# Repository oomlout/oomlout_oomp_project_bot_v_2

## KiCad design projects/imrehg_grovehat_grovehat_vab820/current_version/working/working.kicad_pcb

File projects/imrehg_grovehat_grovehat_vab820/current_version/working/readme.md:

# grovehat
 
## summary 
* id: imrehg_grovehat_grovehat_vab820
* user: imrehg
* name: grovehat
* board: grovehat_vab820
* repo: https://github.com/imrehg/grovehat
* src_file_repo_kicad_pcb: grovehat-vab820.kicad_pcb
* src_file_repo_kicad_pcb_link: https://github.com/imrehg/grovehat/tree/master/grovehat-vab820.kicad_pcb

* src_file_repo_sch: grovehat-vab820.sch
* src_file_repo_sch_link: https://github.com/imrehg/grovehat/tree/master/grovehat-vab820.sch
* full details link: https://github.com/oomlout/oomlout_oomp_project_bot_v_2/tree/main/projects/imrehg_grovehat_grovehat_vab820/current_version/working

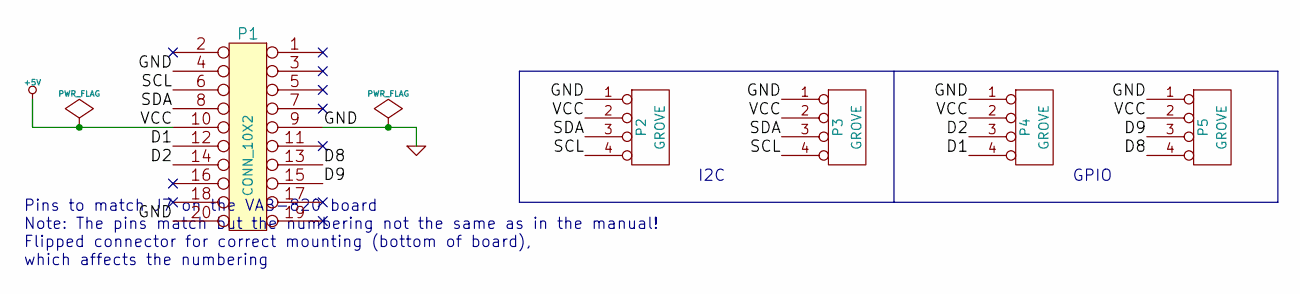
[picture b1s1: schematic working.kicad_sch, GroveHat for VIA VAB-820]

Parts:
P1: CONN_10X2; pin_array_2mm_10x2
P2, P3, P4, P5: GROVE; TWIG_2.0

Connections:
+5V: P1.10, P2.2, P3.2, P4.2, P5.2
/D1: P1.12, P4.4
/D2: P1.14, P4.3
/D8: P1.13, P5.4
/D9: P1.15, P5.3
/SCL: P1.6, P2.4, P3.4
/SDA: P1.8, P2.3, P3.3
GND: P1.4, P1.9, P1.20, P2.1, P3.1, P4.1, P5.1

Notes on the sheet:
Pins to match J7 on the VAB-820 board Note: The pins match but the numbering not the same as in the manual! Flipped connector for correct mounting (bottom of board), which affects the numbering
I2C
GPIO

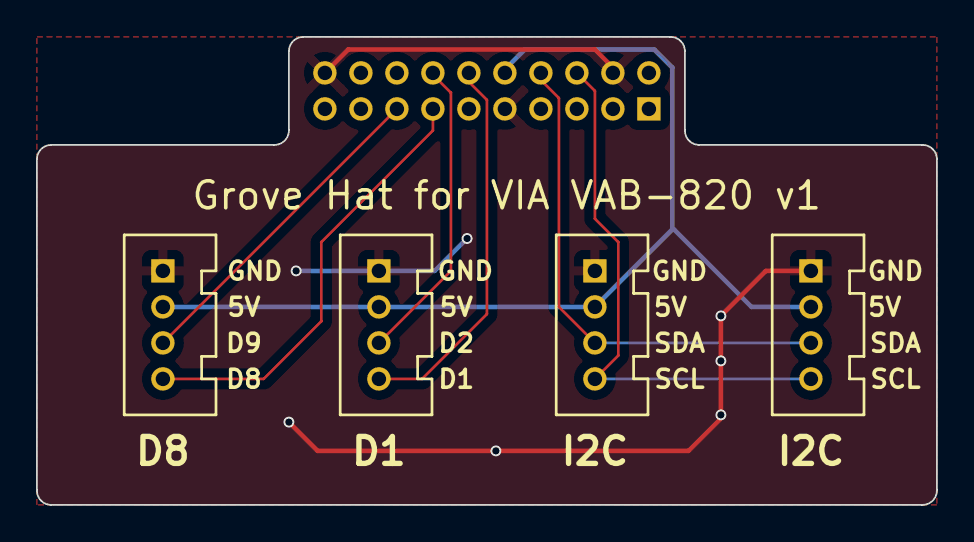
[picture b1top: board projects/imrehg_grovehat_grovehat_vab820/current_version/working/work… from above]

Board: 2 copper layers, 50.0 x 26.0 mm, 5 parts (1 on the bottom side), 8 nets.

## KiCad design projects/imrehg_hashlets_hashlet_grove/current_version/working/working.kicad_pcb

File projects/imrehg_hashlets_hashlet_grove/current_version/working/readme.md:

# hashlets
 
## summary 
* id: imrehg_hashlets_hashlet_grove
* user: imrehg
* name: hashlets
* board: hashlet_grove
* repo: https://github.com/imrehg/hashlets
* src_file_repo_kicad_pcb: grove/hashlet-grove.kicad_pcb
* src_file_repo_kicad_pcb_link: https://github.com/imrehg/hashlets/tree/master/grove/hashlet-grove.kicad_pcb

* src_file_repo_sch: grove/hashlet-grove.sch
* src_file_repo_sch_link: https://github.com/imrehg/hashlets/tree/master/grove/hashlet-grove.sch
* full details link: https://github.com/oomlout/oomlout_oomp_project_bot_v_2/tree/main/projects/imrehg_hashlets_hashlet_grove/current_version/working

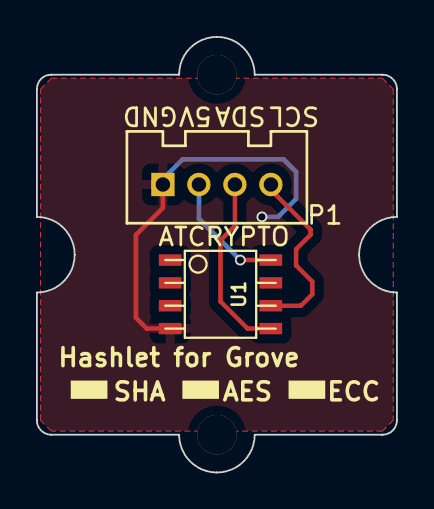
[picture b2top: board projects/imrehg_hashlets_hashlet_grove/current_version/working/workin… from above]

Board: 2 copper layers, 20.0 x 24.2 mm, 4 parts (0 on the bottom side), 4 nets.

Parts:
HoleA: P***; 1pin
HoleB: P***; 1pin
P1: TWIG_2.0
U1: ATCRYPTO; so-8

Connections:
/SCL: P1.4, U1.6
/SDA: P1.3, U1.5
/VCC: P1.2, U1.8
GND: P1.1, U1.4

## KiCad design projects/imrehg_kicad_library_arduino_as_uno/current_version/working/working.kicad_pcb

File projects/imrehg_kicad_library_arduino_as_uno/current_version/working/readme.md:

# kicad_library
 
## summary 
* id: imrehg_kicad_library_arduino_as_uno
* user: imrehg
* name: kicad_library
* board: arduino_as_uno
* repo: https://github.com/imrehg/kicad-library
* src_file_repo_kicad_pcb: template/Arduino_As_Uno_R3/Arduino_As_Uno.kicad_pcb
* src_file_repo_kicad_pcb_link: https://github.com/imrehg/kicad-library/tree/master/template/Arduino_As_Uno_R3/Arduino_As_Uno.kicad_pcb

* src_file_repo_sch: template/Arduino_As_Uno_R3/Arduino_As_Uno.sch
* src_file_repo_sch_link: https://github.com/imrehg/kicad-library/tree/master/template/Arduino_As_Uno_R3/Arduino_As_Uno.sch
* full details link: https://github.com/oomlout/oomlout_oomp_project_bot_v_2/tree/main/projects/imrehg_kicad_library_arduino_as_uno/current_version/working

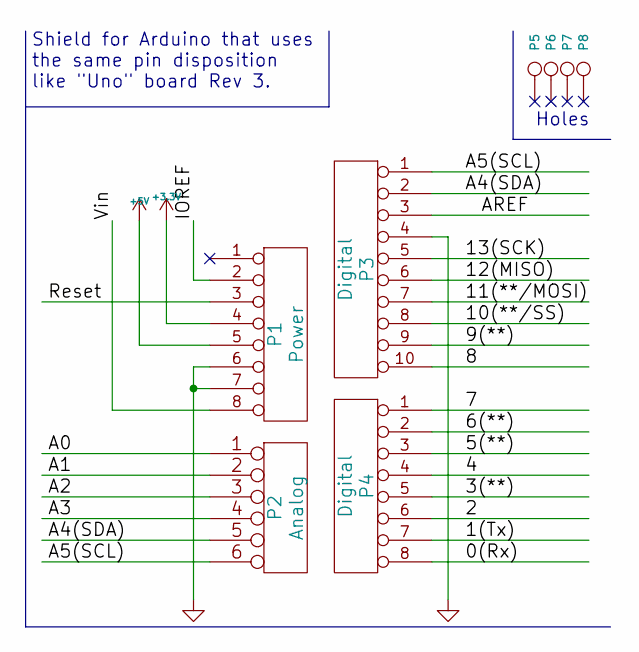
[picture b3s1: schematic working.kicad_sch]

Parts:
P1: Power; Socket_Strip_Arduino_1x08
P2: Analog; Socket_Strip_Arduino_1x06
P3: Digital; Socket_Strip_Arduino_1x10
P4: Digital; Socket_Strip_Arduino_1x08
P5, P6, P7, P8: CONN_1; Arduino_1pin

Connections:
+3V3: P1.4
+5V: P1.5
/0(Rx): P4.8
/1(Tx): P4.7
/2: P4.6
/3(**): P4.5
/4: P4.4
/5(**): P4.3
/6(**): P4.2
/7: P4.1
/8: P3.10
/9(**): P3.9
/10(**/SS): P3.8
/11(**/MOSI): P3.7
/12(MISO): P3.6
/13(SCK): P3.5
/A0: P2.1
/A1: P2.2
/A2: P2.3
/A3: P2.4
/A4(SDA): P2.5, P3.2
/A5(SCL): P2.6, P3.1
/AREF: P3.3
/IOREF: P1.2
/Reset: P1.3
/Vin: P1.8
GND: P1.6, P1.7, P3.4

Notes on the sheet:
Shield for Arduino that uses the same pin disposition like "Uno" board Rev 3.
Holes

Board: 2 copper layers, 8 parts (0 on the bottom side), 3 nets, no tracks yet.

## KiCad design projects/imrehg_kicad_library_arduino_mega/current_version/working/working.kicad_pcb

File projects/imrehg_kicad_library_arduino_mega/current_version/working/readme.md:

# kicad_library
 
## summary 
* id: imrehg_kicad_library_arduino_mega
* user: imrehg
* name: kicad_library
* board: arduino_mega
* repo: https://github.com/imrehg/kicad-library
* src_file_repo_kicad_pcb: template/Arduino_Mega_R3/Arduino_Mega.kicad_pcb
* src_file_repo_kicad_pcb_link: https://github.com/imrehg/kicad-library/tree/master/template/Arduino_Mega_R3/Arduino_Mega.kicad_pcb

* src_file_repo_sch: template/Arduino_Mega_R3/Arduino_Mega.sch
* src_file_repo_sch_link: https://github.com/imrehg/kicad-library/tree/master/template/Arduino_Mega_R3/Arduino_Mega.sch
* full details link: https://github.com/oomlout/oomlout_oomp_project_bot_v_2/tree/main/projects/imrehg_kicad_library_arduino_mega/current_version/working

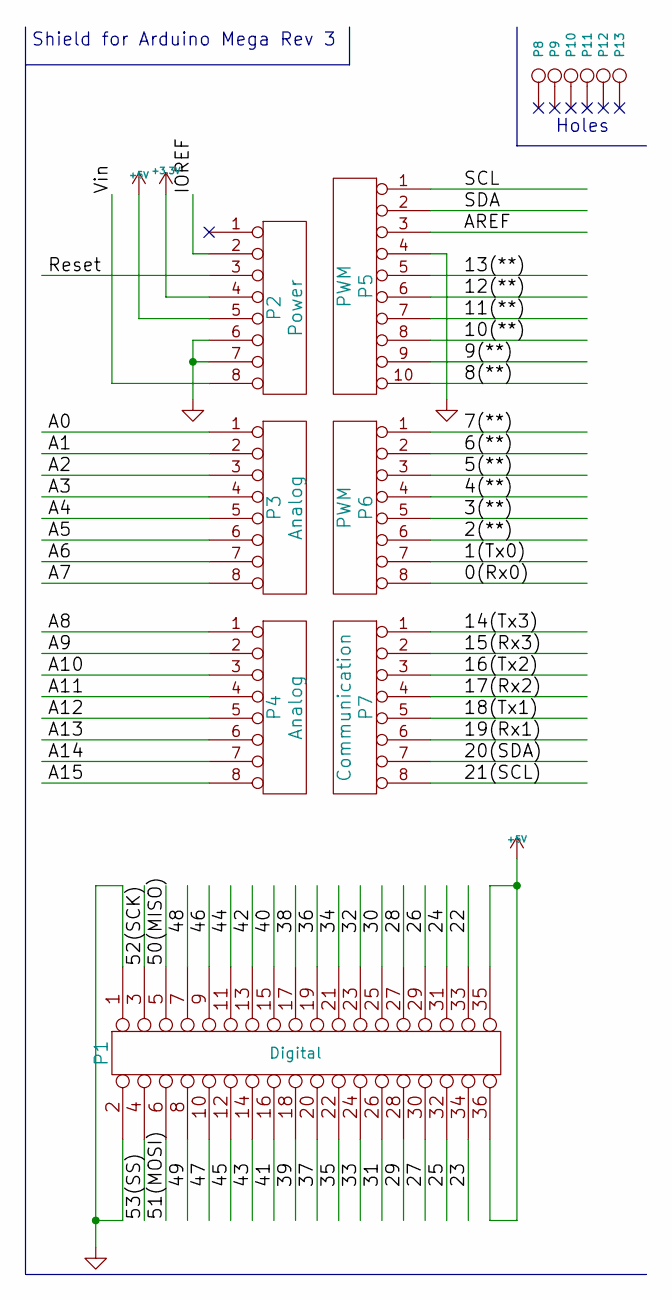
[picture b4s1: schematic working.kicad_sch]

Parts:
P1: Digital; Socket_Strip_Arduino_2x18
P2: Power; Socket_Strip_Arduino_1x08
P3, P4: Analog; Socket_Strip_Arduino_1x08
P5: PWM; Socket_Strip_Arduino_1x10
P6: PWM; Socket_Strip_Arduino_1x08
P7: Communication; Socket_Strip_Arduino_1x08
P8, P9, P10, P11, P12, P13: CONN_1; Arduino_1pin

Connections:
+3V3: P2.4
+5V: P1.35, P1.36, P2.5
/0(Rx0): P6.8
/1(Tx0): P6.7
/2(**): P6.6
/3(**): P6.5
/4(**): P6.4
/5(**): P6.3
/6(**): P6.2
/7(**): P6.1
/8(**): P5.10
/9(**): P5.9
/10(**): P5.8
/11(**): P5.7
/12(**): P5.6
/13(**): P5.5
/14(Tx3): P7.1
/15(Rx3): P7.2
/16(Tx2): P7.3
/17(Rx2): P7.4
/18(Tx1): P7.5
/19(Rx1): P7.6
/20(SDA): P7.7
/21(SCL): P7.8
/22: P1.33
/23: P1.34
/24: P1.31
/25: P1.32
/26: P1.29
/27: P1.30
/28: P1.27
/29: P1.28
/30: P1.25
/31: P1.26
/32: P1.23
/33: P1.24
/34: P1.21
/35: P1.22
/36: P1.19
/37: P1.20
/38: P1.17
/39: P1.18
/40: P1.15
/41: P1.16
/42: P1.13
/43: P1.14
/44: P1.11
/45: P1.12
/46: P1.9
/47: P1.10
/48: P1.7
/49: P1.8
/50(MISO): P1.5
/51(MOSI): P1.6
/52(SCK): P1.3
/53(SS): P1.4
/A0: P3.1
/A1: P3.2
/A2: P3.3
/A3: P3.4
/A4: P3.5
/A5: P3.6
/A6: P3.7
/A7: P3.8
/A8: P4.1
/A9: P4.2
/A10: P4.3
/A11: P4.4
/A12: P4.5
/A13: P4.6
/A14: P4.7
/A15: P4.8
/AREF: P5.3
/IOREF: P2.2
/Reset: P2.3
/SCL: P5.1
/SDA: P5.2
/Vin: P2.8
GND: P1.1, P1.2, P2.6, P2.7, P5.4

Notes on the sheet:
Shield for Arduino Mega Rev 3
Holes

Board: 2 copper layers, 13 parts (0 on the bottom side), 2 nets, no tracks yet.

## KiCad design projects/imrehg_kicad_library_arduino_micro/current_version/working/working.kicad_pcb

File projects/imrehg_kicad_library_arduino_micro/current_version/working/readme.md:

# kicad_library
 
## summary 
* id: imrehg_kicad_library_arduino_micro
* user: imrehg
* name: kicad_library
* board: arduino_micro
* repo: https://github.com/imrehg/kicad-library
* src_file_repo_kicad_pcb: template/Arduino_Micro/Arduino_Micro.kicad_pcb
* src_file_repo_kicad_pcb_link: https://github.com/imrehg/kicad-library/tree/master/template/Arduino_Micro/Arduino_Micro.kicad_pcb

* src_file_repo_sch: template/Arduino_Micro/Arduino_Micro.sch
* src_file_repo_sch_link: https://github.com/imrehg/kicad-library/tree/master/template/Arduino_Micro/Arduino_Micro.sch
* full details link: https://github.com/oomlout/oomlout_oomp_project_bot_v_2/tree/main/projects/imrehg_kicad_library_arduino_micro/current_version/working

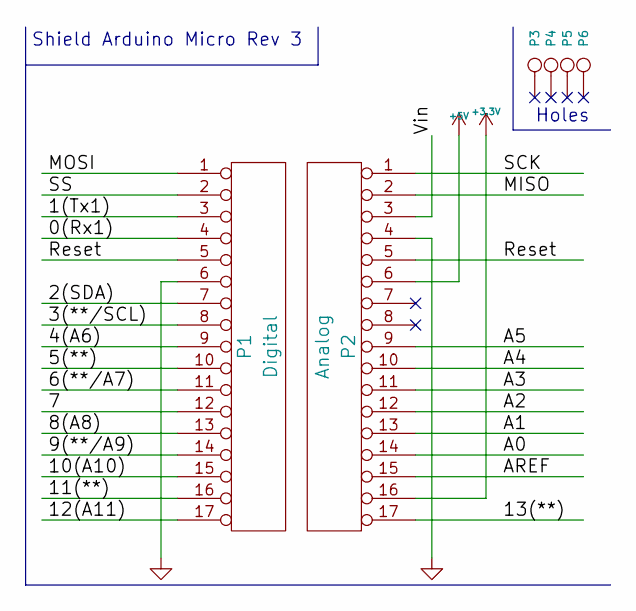
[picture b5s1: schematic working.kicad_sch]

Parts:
P1: Digital; Socket_Strip_Arduino_1x17
P2: Analog; Socket_Strip_Arduino_1x17
P3, P4, P5, P6: CONN_1; 1pin_Micro

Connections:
+3V3: P2.16
+5V: P2.6
/0(Rx1): P1.4
/1(Tx1): P1.3
/2(SDA): P1.7
/3(**/SCL): P1.8
/4(A6): P1.9
/5(**): P1.10
/6(**/A7): P1.11
/7: P1.12
/8(A8): P1.13
/9(**/A9): P1.14
/10(A10): P1.15
/11(**): P1.16
/12(A11): P1.17
/13(**): P2.17
/A0: P2.14
/A1: P2.13
/A2: P2.12
/A3: P2.11
/A4: P2.10
/A5: P2.9
/AREF: P2.15
/MISO: P2.2
/MOSI: P1.1
/Reset: P1.5, P2.5
/SCK: P2.1
/SS: P1.2
/Vin: P2.3
GND: P1.6, P2.4

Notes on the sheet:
Holes
Shield Arduino Micro Rev 3

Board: 2 copper layers, 6 parts (0 on the bottom side), 2 nets, no tracks yet.

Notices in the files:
projects/imrehg_grovehat_grovehat_vab820/current_version/working/working.kicad_pcb:
CERN Open Hardware License 1.2
CERN OHL 1.2
projects/imrehg_hashlets_hashlet_grove/current_version/working/working.kicad_pcb:
CC-BY-SA 3.0
